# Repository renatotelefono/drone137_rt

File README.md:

# drone137

Local visual reconnaissance development for a confined space. The first runnable
product is a browser recon lab with a Python controller, a small local model
manager, and repeatable Three.js environments. No TypeScript or hosted inference is used.

**Pre-hardware build preparation:** [six-item status and evidence](docs/pre-hardware-six.md), [prototype assembly files](hardware/esp32/indoor/scout-110-bench/assembly.md) and [firmware/commissioning guide](hardware/esp32/flight/README.md). Safe builds keep motors disabled; no physical flight is qualified.
[Supported aircraft](docs/supported-aircraft.md) defines what the program can fly and the contract any aircraft must meet; the [builder brief](hardware/esp32/indoor/scout-110-bench/builder-brief.md) is the hand-off for building the Scout 110-B.

**Microquad component lab:** `/components` stores swappable parts and pinned
assemblies in SQLite, with Rapier rigid-body physics rendered by Three.js.
Run it alone with `python -m scripts.component_lab --port 8152`. The five indoor
designs and two reference variants have completed a 42-case simulation study;
unmeasured component assumptions and failed gates remain explicit. See
[data sources, engine choice, results and limitations](docs/component-physics.md).
The revised controller and explicitly revised battery hypotheses complete 40/42
flight cases (95.2%), also 400/420 across additional noise seeds. The original
assemblies remain available; hardware, camera recognition and the revised
under-$50 parts budget are not qualified by this physics benchmark.

**Ask the console:** a typed or dictated request such as "connect to the workshop scout" is mapped by the local model to one console action from a fixed list and run by the service with its usual checks; launches still go through the reviewed plan. See [mission-control.md](docs/mission-control.md).

**Docking:** a mission can end on dock A, a printed landing base with contact charging and a tag column; the aircraft returns, aligns on the tags, lands in the funnel and charges, and the dock pose becomes the map origin. Registry, dock controller API, the simulated dock and the twenty-docking gate are in [docking.md](docs/docking.md); the hardware is in `hardware/esp32/indoor/scout-110-bench/dock/`.

**Watch from the dock:** a docked aircraft keeps its camera on; motion and change are detected on every frame, the local model says what an event was from a before-and-after picture, and the console raises the alert with the evidence; whether a thing was added, taken away or moved is read from the pixels, a person is a dedicated detector's call, the model names the thing. Gated on staged synthetic events and on rendered workshop scenarios from a docked camera, the event category at 90 % on both; real clips can be recorded and played through the same gate. See [watch.md](docs/watch.md).

**Shared airspace:** several aircraft fly at once on one airspace that keeps them 1.5 m apart, gives right of way by number, holds everyone when a link goes quiet, and backs a holding aircraft out of a doorway; three aircraft gated through the benchmark room's one doorway within the 8 GB machine's budget. See [airspace.md](docs/airspace.md).

**Memory before a flight:** every plan shows what it will need against this machine, a measured preflight checks it in seconds, and the memory watch stops a mission that exceeds its budget. See [mission-control.md](docs/mission-control.md).

**Fly by hand:** a console panel for keyboard or gamepad control over the paired link, inside a reduced envelope, with release-to-level and land-on-silence; for commissioning, never for missions.

**Mission wizard:** the console opens with a Start-here panel that proposes the four mission clusters, map, audit, watch and find, from place memory and mission state, composes the brief for the one it can fly, and starts simulated exploration flights directly. See [mission-control.md](docs/mission-control.md).

**Mission control:** `/control` now connects the SQLite aircraft assembly to
Rapier flight, a service-owned Three.js camera, local Qwen plus Florence image
verification, two-view localization, return/landing and video evidence. Write a
red fire extinguisher search brief, choose an inspection area and aircraft, review
the plan and launch. Flight/recording continue when the operator dashboard closes.
One aircraft flies at a time. The rectangle selects inspection stations; transit
can leave it. Known map geometry and ideal external positioning remain assumptions.
See [mission setup, API, tests and limitations](docs/mission-runtime.md).
The Scout 110-B completed **24/24 full missions** across eight known synthetic
cases repeated three times, with zero false confirmations, decodable video and
a 4.26 GiB peak application-memory measurement on a 16 GiB host. This is separate
from the component-only physics benchmark above. See the
[full mission qualification and retained failures](docs/mission-integration-validation.md).

The earlier sequential two-aircraft, kinematic mission console remains at
`/control-legacy`. It supports inventory, doorway and view-comparison experiments.
Concurrent flight and physical control are not enabled by either dashboard.

**Unknown-place experiment:** `/places` displays environments reconstructed from
onboard RGB images and synthetic IMU data, with named places, individual visits,
maps and image-backed model observations saved in SQLite. The experimental
OpenVINS mapper starts without a room map or true-position feedback. Development
flights now pass all gates, but the latest fresh-layout suite passed only **2/3**:
one flight stopped on the link watchdog. Development-79 passes after diagnostic
I/O isolation; a new frozen suite is running. Reliable unfamiliar-environment
exploration remains open; the earlier 24/24 known-map result does not qualify it.
See [the test and current architecture](docs/blind-exploration.md) and
[preserved result summaries](docs/blind-exploration-validation.json).

**Aircraft connection:** Mission Control's **Connect a drone** panel supports
pinned HTTPS pairing, telemetry and camera preview. The ESP32 prototype firmware
now compiles, and its shared C++ controller is exercised through the host adapter
and monitor over local TLS. Recording and calibrated camera/IMU replay are
available. Physical commissioning, control tuning and autonomous-navigation
integration remain outstanding; the dashboard cannot launch a physical aircraft.
See [protocol and local setup](hardware/esp32/link-protocol.md) and the
[current handoff and remaining work](docs/agent-handoff.md).

For the first hardware prototype, use the
[Scout 110-B parts and bench build](hardware/esp32/indoor/scout-110-bench/README.md).
Its $45.09 consumed-parts allowance is not a delivered checkout quote. This
commercial-parts configuration is stored separately from the hypothetical
power-v2 aircraft used by earlier experiments. The final 24-mission qualification
uses the historical Scout 110-B assembly itself. The new printable stack has
an estimated 25.1 g structural mass; its complete mass and delivered cost are
not yet measured. Update the SQLite assembly from the built parts before using
the old simulation numbers as a hardware prediction. Physical control tuning,
component measurements and real indoor positioning remain hardware work.

**Object-location experiment:** compare the current Qwen model with Qwen plus
local Laya on a search for a red fire extinguisher. Both use camera images and
two-view bearing triangulation, with a sampled 5 GiB application-memory guard.
See [setup, protocol and limitations](docs/localization-experiment.md). This is
a separate camera-station experiment; it does not add physical flight control.

**Dense native-flight experiment:** a 120-prop workshop now runs actual PX4/Gazebo
rotor dynamics beneath the Three.js camera. Qwen and Qwen+Laya search during
continuous takeoff, transit, inspection, return and landing, with estimated-pose
triangulation, draft disturbance, telemetry and video evidence. See
[the flight-test protocol](docs/native-flight-experiment.md). The original kinematic product remains at `/control-legacy`; this native PX4 backend is an evaluation lab. The newer `/control` uses the component-based Rapier backend described above.
The [identity improvement experiment](docs/identity-improvement.md) separates
visible-part checks from triangulation and compares the 2B and 4B vision models
without loading both together. Its saved-frame diagnostic is not a real-world
qualification score.
The revised 2B full-flight batch completed 3/4 jobs with no false location
claims; 4B completed 1/4 under the same checks. A later 2B low-light repeat
passed, but the earlier miss remains evidence of inconsistent recognition.

The [real-room qualification plan](docs/real-room-qualification.md) adds a frozen
eight-mission challenge for Qwen 2B plus Laya: unfamiliar furniture arrangements,
paired present/absent targets, partial occlusion, glare/dim/blur conditions and
delayed/dropped camera frames. It also documents where offline Glob3R room
reconstruction can help, what remains unimplemented, and why a finite all-pass
test does not establish universal 100% accuracy.
Its first hard-suite Qwen + Laya run scored **5/8**, including one wrong-object
claim; all eight flights landed. Peak application guard memory was 3.48 GiB on
the 16 GiB host. The target-present success rate was 1/4, so reliable object
verification remains unresolved despite successful flight execution.

The [imported asset experiment](docs/online-assets-experiment.md) adds CC0
extinguisher, cart, shelving and crate models plus photographed workshop HDR
lighting, all bundled locally with verified hashes and aligned collision bounds.
The same Qwen 2B + Laya hard suite scored **6/8**, with two target-present
successes, one miss and one wrong-object claim. All eight flights landed;
peak application guard memory was **3.54 GiB** on the 16 GiB host. Use
`--assets polyhaven` with `scripts.evaluate_flight` to reproduce this variant.
The scene is assembled from assets, not a reconstructed real building.

The [efficiency audit](docs/efficiency.md) makes route planning 8.25× faster in
a 40-route CPU benchmark with identical paths. Fixed-input repeats reproduced
16/16 vision outputs and 22/22 Laya choices; 133 tests and a native flight smoke
test passed. This is a behavior-preserving planner optimization, not a new full
mission accuracy result or an end-to-end speedup claim.

## Start on a Mac

Requires Python 3.11–3.14 and a current browser with WebGL and MediaRecorder.
The model runtime installer targets **Apple Silicon**; Intel Macs and actual
8 GiB performance have not been validated. Local Qwen/Metal runs on the tested M4
with 16 GiB; recognition accuracy still needs improvement.

```bash
git clone https://github.com/bitfent/drone137.git
cd drone137
./scripts/bootstrap-macos.sh --minimal
./scripts/run-local.sh --mode recon --open-browser
```

Alternatively, open **Start drone137.command** in the extracted project. The
launcher bootstraps the small Python environment if missing and opens the local
console. If Finder blocks execution, run the shell commands above in Terminal.
The service binds only to `127.0.0.1:8137`; Ctrl-C stops its owned processes.

For model installation and the earlier single-aircraft smoke test, open
`http://127.0.0.1:8137/`:

1. Choose **Scripted demo · no AI**, generate a room seed, and **Start recon** to
   test rendering, navigation, recording and failure handling without model weights.
2. For local vision, install Xcode command-line tools (`xcode-select --install`),
   Git and CMake (`brew install cmake`, assuming Homebrew is already installed).
3. Click **Install runtime**, then **Download / resume model**. The manager builds
   pinned llama.cpp and retrieves Qwen3-VL-2B-Instruct Q4_K_M plus its Q8_0 vision
   projector. It pins the official model commit and verifies both SHA256 hashes.
4. **Start model**, **Test vision**, then select **Local Qwen vision** and start a
   mission. A failed vision check needs investigation before relying on observations.

The GUI exposes progress, errors, cancellation, file verification, bounded logs,
and model stop/restart. Interrupted downloads retain resumable partials. Corrupt
installed files are preserved for inspection; they are never silently used.
Keep 10 GiB free **in addition** to remaining model downloads or the 4 GiB runtime
build allowance. Actual combined resource use still needs measurement on the Mac.

## Start on Windows

Ported, not yet run on Windows: see [windows.md](docs/windows.md) for the hand-over. On a
Windows 11 x64 machine with a GPU, clone the repo and double-click `Start drone137.bat`, or in
PowerShell:

```
powershell -ExecutionPolicy Bypass -File scripts\bootstrap-windows.ps1 --minimal
scripts\run-local.ps1 --mode recon --open-browser
```

The console's "Install runtime" unpacks a pinned llama.cpp release (Vulkan by default, CUDA or
CPU with `DRONE137_RUNTIME_BACKEND`); the person detector comes from
`python -m scripts.fetch_person_model`.

## What the virtual product does

- Generates repeatable random rooms, warehouse aisles and connected rooms.
- Runs inspection-point patrols with baseline and obstructed-passage variants;
  returns with a partial report when an inspection point cannot be reached.
- Simulates ideal pose and planar range sensing; builds an observed occupancy map.
- Plans clearance-aware routes through observed free cells, explores new areas,
  and returns home after up to 12 observations. Mission deadline: 180 seconds.
- Provides overhead and onboard cameras. The local model sees selected fresh
  320 × 240 JPEGs and can continue, request one additional left/right view, hold,
  or finish an exploration. Patrols restrict it to continue, extra views or hold;
  one blank view cannot finish the whole patrol. The model cannot issue arbitrary
  coordinates or motor commands.
- Runs range supervision independently of inference; sensor loss, browser/camera
  loss, inference errors and operator intervention stop motion.
- Records browser video (WebM or MP4), selected images, pose/event timestamps,
  scene seed and observations. Saved missions open an HTML report with video
  seek links, images, observed map, route and unreached points. Matching local-model
  patrols compare independently classified images at aligned viewpoints and flag
  a new obstruction when open space becomes a solid surface. Evidence shares a 1 GiB cap.

The mission-control dashboard is a **fixed-altitude kinematic sandbox**. The
separate native-flight evaluation lab above uses PX4/Gazebo dynamics; neither
path has been qualified against a physical aircraft.
Map-observed percentage is geometric sensor coverage, not camera visibility or
semantic recognition accuracy. Sensors/pose are ideal; there is no SLAM, sensor
noise, dynamic-obstacle prediction, full 3D planning or physical drone connection.
Observation seek links use approximate browser video time; exact exposure/pose
alignment remains unverified.
Pause ends autonomous progress; end the mission before starting another. Keep the
browser tab active: camera/browser loss stops the virtual mission after 2 seconds.

## Validation and current limits

**Simulation versus real-drone comparison:** [test data and comparison tables](docs/test-comparison.md)
preserve Scout 110-B component/mission results, blind-mapping failures, the
historical vision-model comparison and separate software-test counts. A
[frozen JSON baseline](docs/test-data/pre-hardware-2026-10-23.json) retains exact
values and source hashes, and a [physical-run template](docs/test-data/hardware-run-template.json)
is ready for measured hardware results. No physical flight results exist yet;
unmeasured values stay empty rather than being presented as passes.

Real-world reliability is now tracked separately for **workshops, warehouses,
building perimeters, flat fields and hillsides**. All five remain unqualified.
The frozen real-camera smoke test found 11 of 12 labelled object names across six
public indoor images, with one missed object group. This is diagnostic evidence,
not a general accuracy or flight claim. The [reliability protocol](docs/reliability-protocol.md)
defines data collection, site separation, proposed thresholds and commands to
evaluate local camera clips without flying a drone. Full-caption precision and
site-specific data remain missing.

Current Mac and historical Linux evidence is in [docs/validation.md](docs/validation.md).
The M4 build ran actual Qwen/Metal patrols, recorded playable video and generated
reports. The original closed-gate and changed-passage misses are retained as
regressions. Separating image evidence from action selection, with settings for each camera
profile, passes all 32 center-classification cases (24 rendered views plus eight regressions), with
zero blocked views classified as open. Successful recording/navigation alone does
not prove perception accuracy; the patrol browser test also checks recognition.
104 accelerated geometry scenarios returned with zero clearance violations. A
separate real-Qwen PX4/Gazebo gate route correctly classified both gates and
returned to land; indoor patrol is not yet connected to that dynamics backend.
The GUI reports failures explicitly and never switches to scripted decisions itself.

For richer visual inspections, choose **Detailed workshop · 720p → Baseline →
Patrol inspection points**. The scene contains stocked shelving, labeled cartons,
a workbench with monitor/keyboard/toolbox/vise/cable, drums on a pallet, a hand
truck, tool drawers, a plant and a fire extinguisher. Geometry and canvas labels
are generated locally; there are no runtime asset downloads. The report adds a
whole-image object description and visible uncertainty beside each camera image.

The workshop records **1280 × 720 at a requested 15 fps**, with **960 × 540** model
snapshots. Its 41° vertical field of view approximates the standard Camera Module 3
candidate in the project brief ([manufacturer specifications](https://www.raspberrypi.com/documentation/accessories/camera.html)).
This is an ideal rendered camera, not a calibrated physical-camera or photorealism
benchmark. Use **Enlarge camera** to inspect the detail. Older simple scenes retain
their 320 × 240 profile.

Choose **Camera realism bay · 720p** for bottles, a wheeled chair and a safety cone
alongside the stocked workshop and cluttered bench. Its local scanned concrete
maps add surface detail. **Camera conditions** selects nominal, low light, glare,
or blur/shift stress. The camera points down 10°; exposure, noise, blur, lens warp
and vignetting are synthetic settings, not hardware calibration. The displayed
camera, recorded video and model snapshots share that processed image. Conditions
are saved in each report and must match when selecting a comparison baseline.
Geometry/range sensing and fixed-height motion still use the ideal sandbox.

To try the product: choose **Warehouse aisle → Baseline → Patrol inspection points**,
start a patrol, open its report, then load **Passage obstructed** and repeat. Use
Local Qwen for observations, or Scripted demo to test the pipeline without inference.

The [Mac handoff](docs/handoff.md) contains transfer, startup and acceptance steps.
[Recon objective](docs/recon-objective.md) separates implemented workflow from the
remaining localization, camera-coverage and flight-dynamics work.

## Development

```bash
# Linux/cloud, or a development machine with Python 3.11–3.14:
./scripts/bootstrap-cloud.sh --minimal
./scripts/test-portable.sh
./scripts/run-local.sh --mode recon
# A second terminal can stop this app:
./scripts/stop-local.sh
```

Three.js 0.180.0 is vendored with its MIT licence and verified npm integrity
metadata, so the GUI does not require Node, npm or a CDN at runtime. Python
packages are installed from hash-locked requirements. Source export:

```bash
./scripts/export-handoff.sh
```

`dist/drone137-source.tar.gz` and its checksum sidecar exclude model weights,
virtual environments, native builds, caches and bulk run evidence. Configurable
paths: `DRONE137_DATA_DIR` (default `.local/data`) and `DRONE137_BUILD_DIR`
(default `.local/build`). Completed runs remain under `.local/data/runs/<episode>`;
no automatic evidence deletion occurs.

Optional browser integration test, using an installed Chromium:

```bash
npm install --prefix .local/browser-test playwright@1.58.2
# With the recon app running; set CHROMIUM_PATH for your browser:
CHROMIUM_PATH="/Applications/Google Chrome.app/Contents/MacOS/Google Chrome" node scripts/check-browser.cjs
# Two rendered warehouse patrols; real Qwen must already be running:
DRONE137_TEST_POLICY=qwen node scripts/check-patrol.cjs
# Fresh rendered perception cases, scored with the same production model pipeline:
node scripts/render-vision-cases.cjs
.venv/bin/python -m scripts.evaluate_perception
# Detailed camera/object recognition and complete workshop patrols:
node scripts/render-detail-cases.cjs
.venv/bin/python -m scripts.evaluate_detail
DRONE137_TEST_POLICY=qwen DRONE137_TEST_SCENARIO=workshop node scripts/check-patrol.cjs
# Accelerated navigation-only suite, no browser/model/dynamics:
.venv/bin/python -m scripts.evaluate_recon --episodes 100
# Production camera stress set (local model ready, no active mission):
DRONE137_REALISM_CASES=.local/validation/my-realism-cases node scripts/render-realism-cases.cjs
.venv/bin/python -m scripts.evaluate_reliability freeze --manifest .local/validation/my-realism-cases/manifest.json --lock .local/validation/my-realism-cases/frozen.json
.venv/bin/python -m scripts.evaluate_reliability run --manifest .local/validation/my-realism-cases/manifest.json --lock .local/validation/my-realism-cases/frozen.json --output .local/validation/my-realism-results
DRONE137_TEST_POLICY=qwen DRONE137_TEST_SCENARIO=realism node scripts/check-patrol.cjs

# Frozen real-image/recorded-video evaluation: see docs/reliability-protocol.md
.venv/bin/python -m scripts.evaluate_reliability --help
```

The scripted browser check exercises a full mission, decodes its video, runs a
sensor failure mission. Set `DRONE137_EXPECT_MODEL_NETWORK_BLOCK=1` only on this
restricted cloud network to also exercise its expected HTTP 403 download error. It is an optional developer check, not a product dependency.

Legacy gate fixture:

```bash
./scripts/run-local.sh --mode fixture --profile cloud-dev --policy scripted
./scripts/evaluate.sh --suite smoke --mode fixture --episodes 2
```

Native Gazebo/PX4 gate integration remains experimental and requires separate
large installations. See `docs/handoff.md`; it does not yet implement indoor recon.

The [hardware realism workbench](docs/hardware-realism.md) adds a SQLite aircraft
library, frozen quadcopter profiles, parameterized optics, GPS-disabled native
sensor emulation, observed-map routing and offline camera/room/motor calibration
tools. Open `/airframes` from mission control. Profiles are provisional until
measurements are supplied; native comparisons run sequentially.

The optional live vision comparison flies Qwen alone, Qwen + Florence-2-base-ft,
and Qwen + SmolVLM2-500M through the same four glare/occlusion missions, including
target-absent controls. Each companion receives live camera crops; Qwen supervises
search in all three arms. The aircraft must first pass measured rotor-joint,
lift-off, hover and landing checks. This is a synthetic development benchmark,
not physical-world qualification. The application guard is 5 GiB, leaving intended
headroom on an 8 GB host; actual 8 GB hardware still requires validation.

```bash
python3.12 -m venv .local/vision-env
.local/vision-env/bin/python -m pip install -r requirements-vision-reviewers.txt
.local/vision-env/bin/python scripts/download_vision_reviewers.py
# Requires the existing native simulator, camera runtime and idle local Qwen app.
.local/laya-env/bin/python -m scripts.evaluate_flight \
  --output .local/validation/my-aircraft-check --suite realism --assets polyhaven \
  --airframes reference-quad@1 --navigation observed --smoke \
  --cases realism-east-motion-present
.local/laya-env/bin/python -m scripts.compare_vision_flights \
  --output .local/validation/my-vision-flight-comparison \
  --preflight .local/validation/my-aircraft-check/results.json
```

Use new output directories for each attempt. Reports retain failed missions and
separate physical flight checks, targets found, false location claims, latency,
memory and full acceptance. Checkpoint revisions and file hashes are recorded.

Measured live results and their limits are in
[the flight comparison](docs/vision-flight-comparison.md). For a separate bounded
closer-view experiment, add `--inspection-policy active-v2` to `evaluate_flight`.
This changes evidence acquisition while retaining the original identity gates;
keep it separate from comparisons of models under the default inspection policy.

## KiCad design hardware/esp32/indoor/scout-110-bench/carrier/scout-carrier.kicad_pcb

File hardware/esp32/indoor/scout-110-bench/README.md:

# Build choice: D137 Scout 110-B

**Swiss procurement (24 October):** [procurement-ch.md](procurement-ch.md) lists Swiss sources, prices, stock and the two substitutions found.

**24 October build update:** [Prototype A assembly package](assembly.md) now includes the schematic, routed carrier, Gerbers and five printable parts. [Flight firmware and commissioning tools](../../flight/README.md) compile and have software tests. Physical fit, power, timing and flight tuning remain unmeasured. The old mass/profile results below are historical and do not qualify the revised mechanical stack.

Build one **Scout 110-B bench prototype** first: a guarded 110 mm quadcopter,
four brushed 8520 motors, a forward-facing XIAO ESP32-S3 Sense camera, and a
single commercial 1S battery. The local computer runs Drone137, Qwen and Florence.
The prototype firmware implements onboard stabilization and command-loss handling;
its physical tuning and timing still need measurement.
No Jetson, onboard language model, Internet connection or mesh network is required.

This is a specific parts choice for camera, electrical and mechanical development.
It is **not a flight-ready kit**: the carrier and firmware are implemented, but
physical fit, electrical performance, control tuning and real indoor positioning
remain unvalidated. The default flight build keeps motor outputs disabled.
Start with camera/IMU recording and frame fit using the current assembly guide.

## Parts to obtain

Core vendor listings rechecked 23 October 2026. USD except where explicitly stated. The
machine-readable [bill of materials](bom.json) records quantities and price bases.

| Part | Quantity | Cost per aircraft | Purchase reference / basis |
|---|---:|---:|---|
| XIAO ESP32-S3 Sense, supplied camera and antenna | 1 | $13.90 | [Seeed SKU 113991115](https://www.seeedstudio.com/XIAO-ESP32S3-Sense-p-5639.html) |
| GY-521 MPU-6050, 3–5 V module input | 1 | $4.95 | [Qkits SKU MPU-6050](https://store.qkits.com/electronics/3-axis-gyroscope-accelerometer-gy-521.html), USD listing |
| 8520 motors, 1 mm shafts, 2 CW + 2 CCW | 4 | $9.00 allowance | [Unmanned Tech 41C-069-230](https://www.unmannedtechshop.co.uk/products/8520-coreless-brushed-motor-pack-2-x-cw-2-x-ccw), actual listing £6.49 per four-pack |
| HQProp 65 mm ultralight, 1 mm shaft, 2 CW + 2 CCW | 4 | $2.39 | [SpeedyFPV TR21](https://speedyfpv.com/products/hqprop-65mm-ultralight-propeller-set-2x-cw-2x-ccw-gray) |
| BETAFPV 450 mAh 1S BT2.0 pack, SKU 01030002 | 1 | $3.75 allocated | [BETAFPV four-pack $14.99](https://betafpv.com/collections/batt-1s/products/bt2-0-450mah-1s-30c-battery-4pcs) |
| Scout 110 printed structure with guards | Set | $4.00 historical allowance | Use the [Prototype A five-part package](assembly.md); obtain its actual print price |
| AO3400A MOSFETs | 4 | $1.00 allowance | SOT-23, low-side motor switches |
| SS34 Schottky diodes, SMA package | 4 | $0.60 allowance | One flyback diode per motor; the carrier footprint is SMA (DO-214AC), so use an SMA-packaged SS34 (for example MDD) or MBRA340T3G |
| 100 ohm gate resistors + 10 kohm pulldowns | 4 + 4 | $0.20 allowance | One of each per MOSFET |
| Motor suppression and supply capacitors | Set | $0.70 allowance | 4 × 100 nF; 470 uF ≥6.3 V; 47 uF; 100 nF |
| Battery measurement divider/filter | Set | $0.10 allowance | 2 × 100 kohm and 100 nF |
| Carrier, IMU mount and connections | Set | $3.00 allowance | Material only; PCB layout/tooling not included |
| BT2.0 aircraft pigtail, wire, camera mount, strap and fasteners | Set | $1.50 allowance | Short motor-current paths; strain relief |
| **Total consumed parts allowance** | | **$45.09** | **A budget, not a complete retail checkout quote** |

The battery seller requires a four-pack. Buying that pack adds $11.24 of spare
battery inventory, making the listed first-build purchase allowance **$56.33
before shipping, taxes and other order minimums**. A delivered single prototype
under $50 has not been established. The $45.09 figure is per aircraft consumed
parts and includes some unquoted allowances. The motor USD allowance is not a
currency conversion guarantee. Charger, tools, ground computer, Wi-Fi access
point, positioning equipment, labour, PCB engineering and spares are excluded.

The original SpeedyFPV $4.49 motor/propeller kit is sold out in its live product
inventory. Do not base this build on that sale price. The replacement motor pack
and HQProp set were available when checked; their combined loaded thrust/current
has not been published or measured here.

## First-prototype order — 23 October 2026

Order **one prototype**, with spare batteries from the required multipack. Buy the
unsoldered **Sense** camera version of the XIAO; the plain ESP32-S3 board does not
include the camera. The camera streams over local Wi-Fi to the ground computer.

| Order now | Purchase quantity | Listed order price |
| --- | ---: | ---: |
| [Seeed XIAO ESP32-S3 Sense](https://www.seeedstudio.com/XIAO-ESP32S3-Sense-p-5639.html) | 1 | $13.90 |
| [Qkits GY-521 MPU-6050](https://store.qkits.com/electronics/3-axis-gyroscope-accelerometer-gy-521.html) | 1 | $4.95 |
| [Unmanned Tech 8520 motor pack, 2 CW + 2 CCW, 1 mm shafts](https://www.unmannedtechshop.co.uk/products/8520-coreless-brushed-motor-pack-2-x-cw-2-x-ccw) | 1 four-pack | GBP 6.49 |
| [HQProp 65 mm, 1 mm hub, 2 CW + 2 CCW](https://speedyfpv.com/products/hqprop-65mm-ultralight-propeller-set-2x-cw-2x-ccw-gray) | 1 four-pack | $2.39 |
| [BETAFPV 450 mAh 1S BT2.0 batteries](https://betafpv.com/collections/batt-1s/products/bt2-0-450mah-1s-30c-battery-4pcs) | 1 four-pack; fit one battery | $14.99 |
| [BETAFPV BT2.0 Whoop Cable Pigtail](https://betafpv.com/collections/accessories/products/bt2-0-1s-whoop-cable-pigtail) — select **BT2.0 Cable Pigtail**, SKU 00313631 | 1 six-pack; fit one pigtail | $5.99 |

This core order totals **$42.22 plus GBP 6.49**, before frame, carrier, small
electronics, shipping and taxes. This is not the complete aircraft checkout.
The motor, propeller and charger stock/price were also checked against their
retailers' public product-variant data; all were available at the time of checking.
An extra propeller set is useful but is not included in the subtotal.

The remaining electrical parts are listed below so they can be sourced together.
The [Prototype A carrier BOM](assembly.md#populate-the-carrier) now specifies packages and wiring. Physical package fit, supply ripple, current handling and assembled mass still require measurements. Small-component prices
and minimum quantities must be reconfirmed in the cart.

| Component reference | Quantity used on one aircraft | Ordering note |
| --- | ---: | --- |
| [AOS AO3400A, SOT-23, LCSC C20917](https://www.lcsc.com/product-detail/MOSFETs_Alpha-Omega-Semicon_C20917.html) | 4 | Listed minimum 5, about $0.43 per five |
| [MDD SS34, SMA, LCSC C8678](https://www.lcsc.com/product-detail/C8678.html) | 4 | Listed minimum 20, about $0.70 per twenty |
| [100 ohm, 0805, 1%, C17408](https://www.lcsc.com/product-detail/C17408.html) | 4 | MOSFET gate resistors |
| [10 kohm, 0805, 1%, C17414](https://www.lcsc.com/product-detail/C17414.html) | 4 | MOSFET gate pulldowns |
| [100 kohm, 0805, 1%, C149504](https://www.lcsc.com/product-detail/C149504.html) | 2 | Battery measurement divider |
| [100 nF, 50 V X7R, 0805, C1711](https://www.lcsc.com/product-detail/C1711.html) | 6 | Four motor suppression, one electronics decoupling, one ADC filter |
| [470 uF, 10 V, SAMYOUNG KMG, C349987](https://www.lcsc.com/product-detail/Aluminum-Electrolytic-Capacitors-Leaded_SamYoung-Electronics_C349987.html) | 1 | Provisional motor-supply bulk capacitor; validate ripple/ESR under motor load |
| [47 uF, 10 V, SAMYOUNG CLZ, C41428003](https://www.lcsc.com/product-detail/C41428003.html) | 1 | Provisional electronics supply capacitor |
| [26 AWG silicone wire](https://www.adafruit.com/category/product/1970) | Short signal/individual motor leads as needed | Reuse supplied motor leads; keep the main battery lead at the pigtail's 22 AWG |

Print one of each of the five [Prototype A parts](assembly.md#fabrication-files)
for **dry fitting**. This package replaces the earlier single-frame proposal.
The frame and camera/battery mounting are not mechanically qualified. Check
the purchased component dimensions before ordering a batch; physical fit and
current handling remain unverified. Reprice the revised stack and carrier;
the historical $45.09 allowance is not a quote for the new fabrication package.

Shared bench equipment, separate from aircraft cost:

- [VIFLY WhoopStor 3](https://viflydrone.com/collections/lipro-battery-charger/products/vifly-whoopstor-6-ports-1s-battery-storage-charger-discharger),
  $32.99: BT2.0 charging with selectable 4.20 V. Start at **4.20 V / 0.3 A** for
  this 450 mAh pack. It needs a suitable power source; use a compatible USB-C PD
  supply meeting the manufacturer's 40 W input specification, not a plain 5 V
  USB port. Reuse a suitable supply if already owned. The manufacturer charger
  plus 65 W US supply bundle was unavailable when checked.
- USB-C **data** cable for flashing, soldering equipment, a multimeter, and a
  scale for assembled mass/thrust measurements. Reuse existing tools. Initial
  camera/IMU checks and motor-output checks are performed without propellers.

The earlier $45.09 consumed-parts estimate is retained above for traceability.
It is not a promise of a delivered build below $50; charger, spare inventory and
multiple sellers' shipping alone make that an inappropriate first-order budget.

## Work required before the first flight

1. Fabricate and inspect the Prototype A carrier, dry-fit the printed parts, and document the as-built wiring, motor order and sensor orientation.
2. Flash the motors-disabled prototype flight firmware and verify the implemented IMU, battery and camera paths on the board. Then follow the propeller-free and restrained commissioning stages; verify control timing while camera streaming is active.
3. Connect physical timestamped camera/IMU telemetry to Drone137; validate stale
   data rejection, exclusive control, operator stop and link-loss behaviour on
   the actual board. Host tests against the protocol emulator do not do this.
4. Measure mass, propulsion/current, battery sag and vibration; update the SQLite
   component revisions and repeat the relevant simulations. Complete restrained
   motor/control checks before a brief guarded hover in a protected test space.
5. Demonstrate real indoor position/height feedback and recovery before enabling
   room navigation or mapping. The MPU-6050 is not an indoor position sensor.
   Additional navigation hardware is not yet specified or included in this order.

Current readiness: **parts procurement and camera bench work can begin; physical
flight remains disabled and unqualified**. There has been no hardware flight.

Use the [simulation/real-drone comparison section](../../../../docs/test-comparison.md)
to retain the existing baseline and record the physical measurements. It includes
exact historical results, configuration/source hashes and a blank physical-run
template. Do not overwrite earlier results when measured components are added.

## Battery and mass

Use **one purchased 1S pack**, not a home-built parallel pack. Limit charging to
**4.20 V** for the initial aircraft electronics/motor design. Although this cell
is sold for 4.35 V charging, the current component model limits propulsion to
4.20 V; a 4.35 V fully charged pack is outside this build configuration.
Use a suitable external BT2.0 1S charger set to 4.20 V. Disconnect the flight
battery during initial USB camera setup.

The manufacturer lists 12.7 g for the pack. The registry adds a provisional 1 g
pigtail, estimates usable capacity at 400 mAh under the lower charge limit, and
assumes 0.10 ohm pack resistance. **Capacity and resistance are hypotheses**, not
manufacturer specifications. The historical assembled mass hypothesis is
**63.26 g**, before the revised printable stack. That stack alone has a geometric
25.1 g solid-PETG estimate. Weigh the real prints, wires, boards and pack and
create a new SQLite assembly revision before predicting this prototype's flight.

The tested `scout-110-power-v2` simulation uses a different, hypothetical 1S2P
480 mAh pack. Its mission result must not be transferred to this purchase build.
`scout-110-bench-b@1` is registered separately in SQLite with frozen component
references and explicit evidence labels. Both configurations remain disabled for
physical operation.

The final **qualification-04** batch tested this Scout 110-B assembly directly:
**24/24 complete simulated missions passed**, with zero false confirmations and
zero missed targets. Peak application memory was 4.26 GiB on a 16 GiB host;
actual 8 GB hardware remains untested. Largest location error was 0.662 m against
the unchanged 0.75 m tolerance; the longest mission took 287 seconds against a
300-second deadline. See the [full qualification](../../../../docs/mission-integration-validation.md).
These are three repeats of eight known synthetic cases with an ideal external
position reference and full modeled batteries, not real-world flight validation.

The initial component-only run completed six 20-second scenarios: **5/6 flight
checks passed**. Nominal, gust, link loss, weak motor and pessimistic assumptions
completed; low battery failed. Only **4/6** met the separate 2:1 thrust-reserve
engineering gate. See [the complete results](simulation-checks.json). These use
estimated propulsion and battery parameters, test no image recognition, and do
not establish readiness for physical flight.

## Assemble and bring up in this order

1. **Camera and IMU first, motors disconnected.** Order the Sense version with
   its camera and antenna. Provision and flash the default motors-disabled
   [flight firmware](../../flight/README.md), then connect/record from Drone137.
   Record the actual camera sensor/revision, verify focus and orientation, then
   measure frame latency. The older `camera_bench.ino` remains a separate
   camera-only diagnostic; it does not implement the flight protocol.
2. **Print and dry-fit the frame.** Motor diagonal 110 mm, nominal 8.6 mm bores,
   65 mm propellers with 1 mm hubs. Adjust bores to the actual print and motor.
   Check propeller/guard clearance, shaft engagement and guard stiffness. The
   CAD is an unprinted dimensional prototype. Centre the battery beneath the
   plate and keep the camera and antenna clear of props and motor wiring.
3. **Build the electrical carrier with the propellers removed.** Follow the
   [Prototype A wiring schedule](assembly.md#wiring-and-motor-orientation).
   The ESP32
   GPIO drives a MOSFET gate, never a motor directly. Verify the actual IMU board
   input regulator and 3.3 V I2C levels; confirm its chip identity and orientation.
4. **Measure the exact propulsion and pack.** Record per-motor thrust/current/RPM
   versus duty and loaded voltage, pack sag/capacity, assembled mass and geometry.
   Save new component revisions in `/components`, preserving the original data.
   Repeat the simulation with those revisions. A different motor winding or prop
   pitch is a new propulsion measurement, even when its dimensions are identical.
5. **Flight-control bench testing precedes flight.** Measure and tune the
   implemented IMU estimator, onboard rate loop/mixer, bounded commands,
   telemetry, battery monitoring and command-loss behavior under simultaneous
   Wi-Fi camera load. Real position feedback must replace the simulator's ideal
   reference before room navigation. Begin subsequent flight tests in a protected
   test space after these checks; simulation success alone is not that validation.

## What the simulation proves and what it assumes

The software test flies a component model through a detailed rendered room and
uses local models to inspect its camera images. Known room geometry and an ideal
external position reference remain inputs. It does not prove that an MPU-6050
alone supplies room coordinates, that the selected Wi-Fi camera maintains the
simulated quality, or that a cheap quad can fly autonomously without additional
positioning work. The benchmark images are 960 × 540; current camera bench code
uses 640 × 480. Re-run recognition at the measured real camera settings.

The hardware path is camera → local Wi-Fi → Drone137 on the ground PC → bounded
flight commands → onboard flight controller. The rapid stabilization loop belongs
on the drone, and the language models inspect images and propose mission actions
on the computer. The prototype firmware/host path now has software tests and
board builds; physical mission navigation remains disabled pending measurements.

## Dock

`dock/` holds dock A: a printed funnel base with contact charging and a tag stand, so
the Scout lands, recharges and takes off again without a battery swap. Geometry, wiring,
Swiss parts and the aircraft-side changes are in `dock/README.md`,
`procurement-ch.md` and `assembly.md`; the flight procedure is `docs/docking.md`.

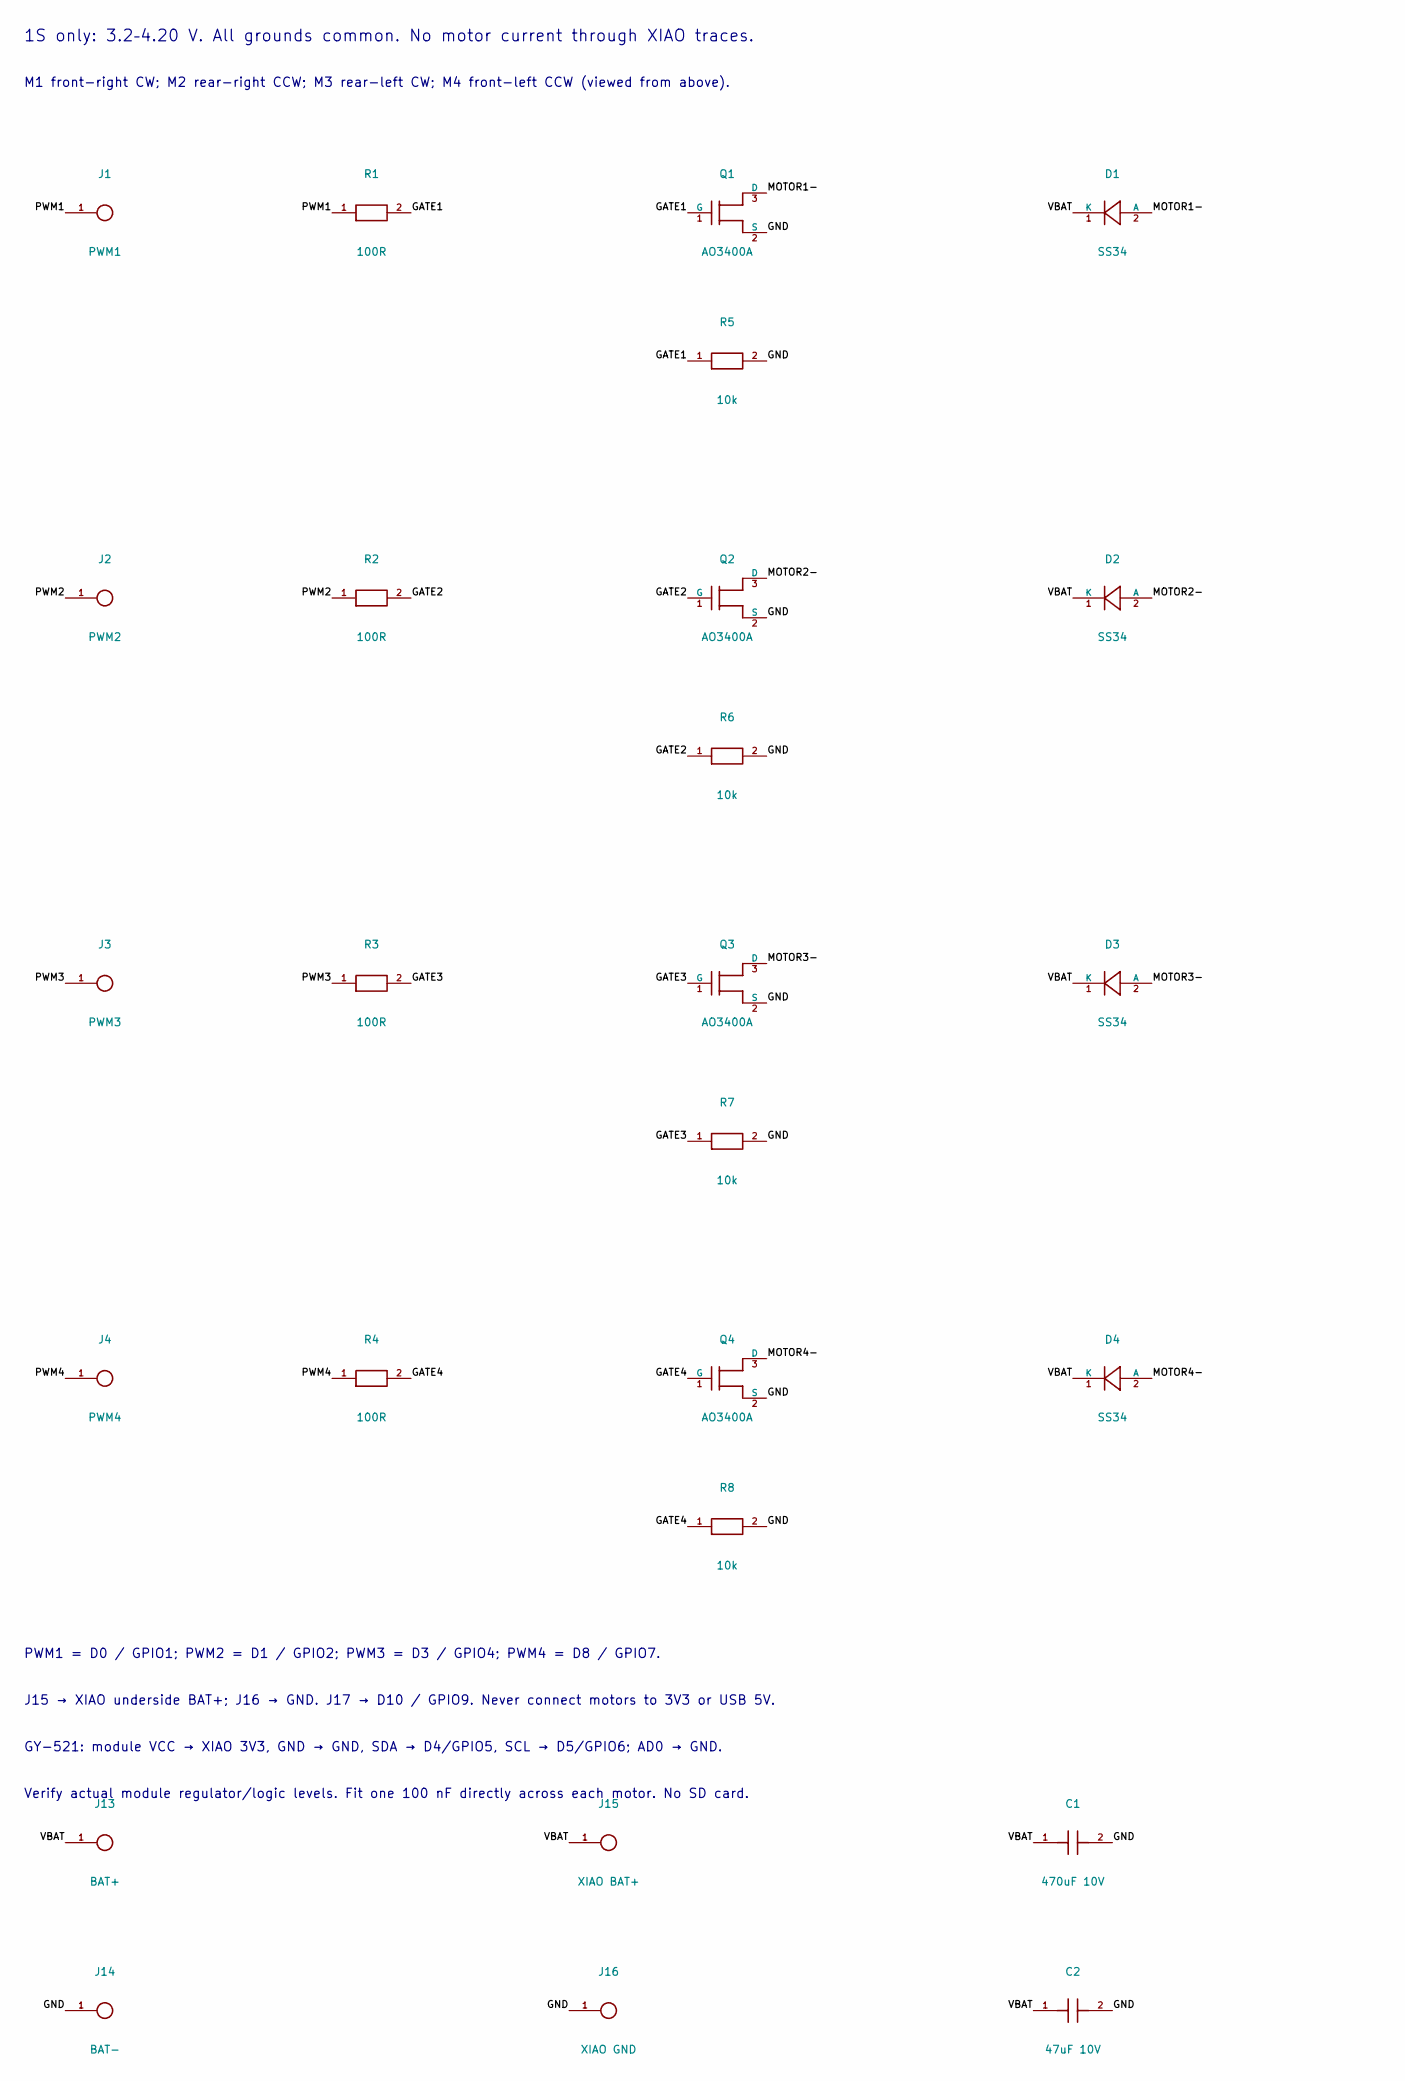
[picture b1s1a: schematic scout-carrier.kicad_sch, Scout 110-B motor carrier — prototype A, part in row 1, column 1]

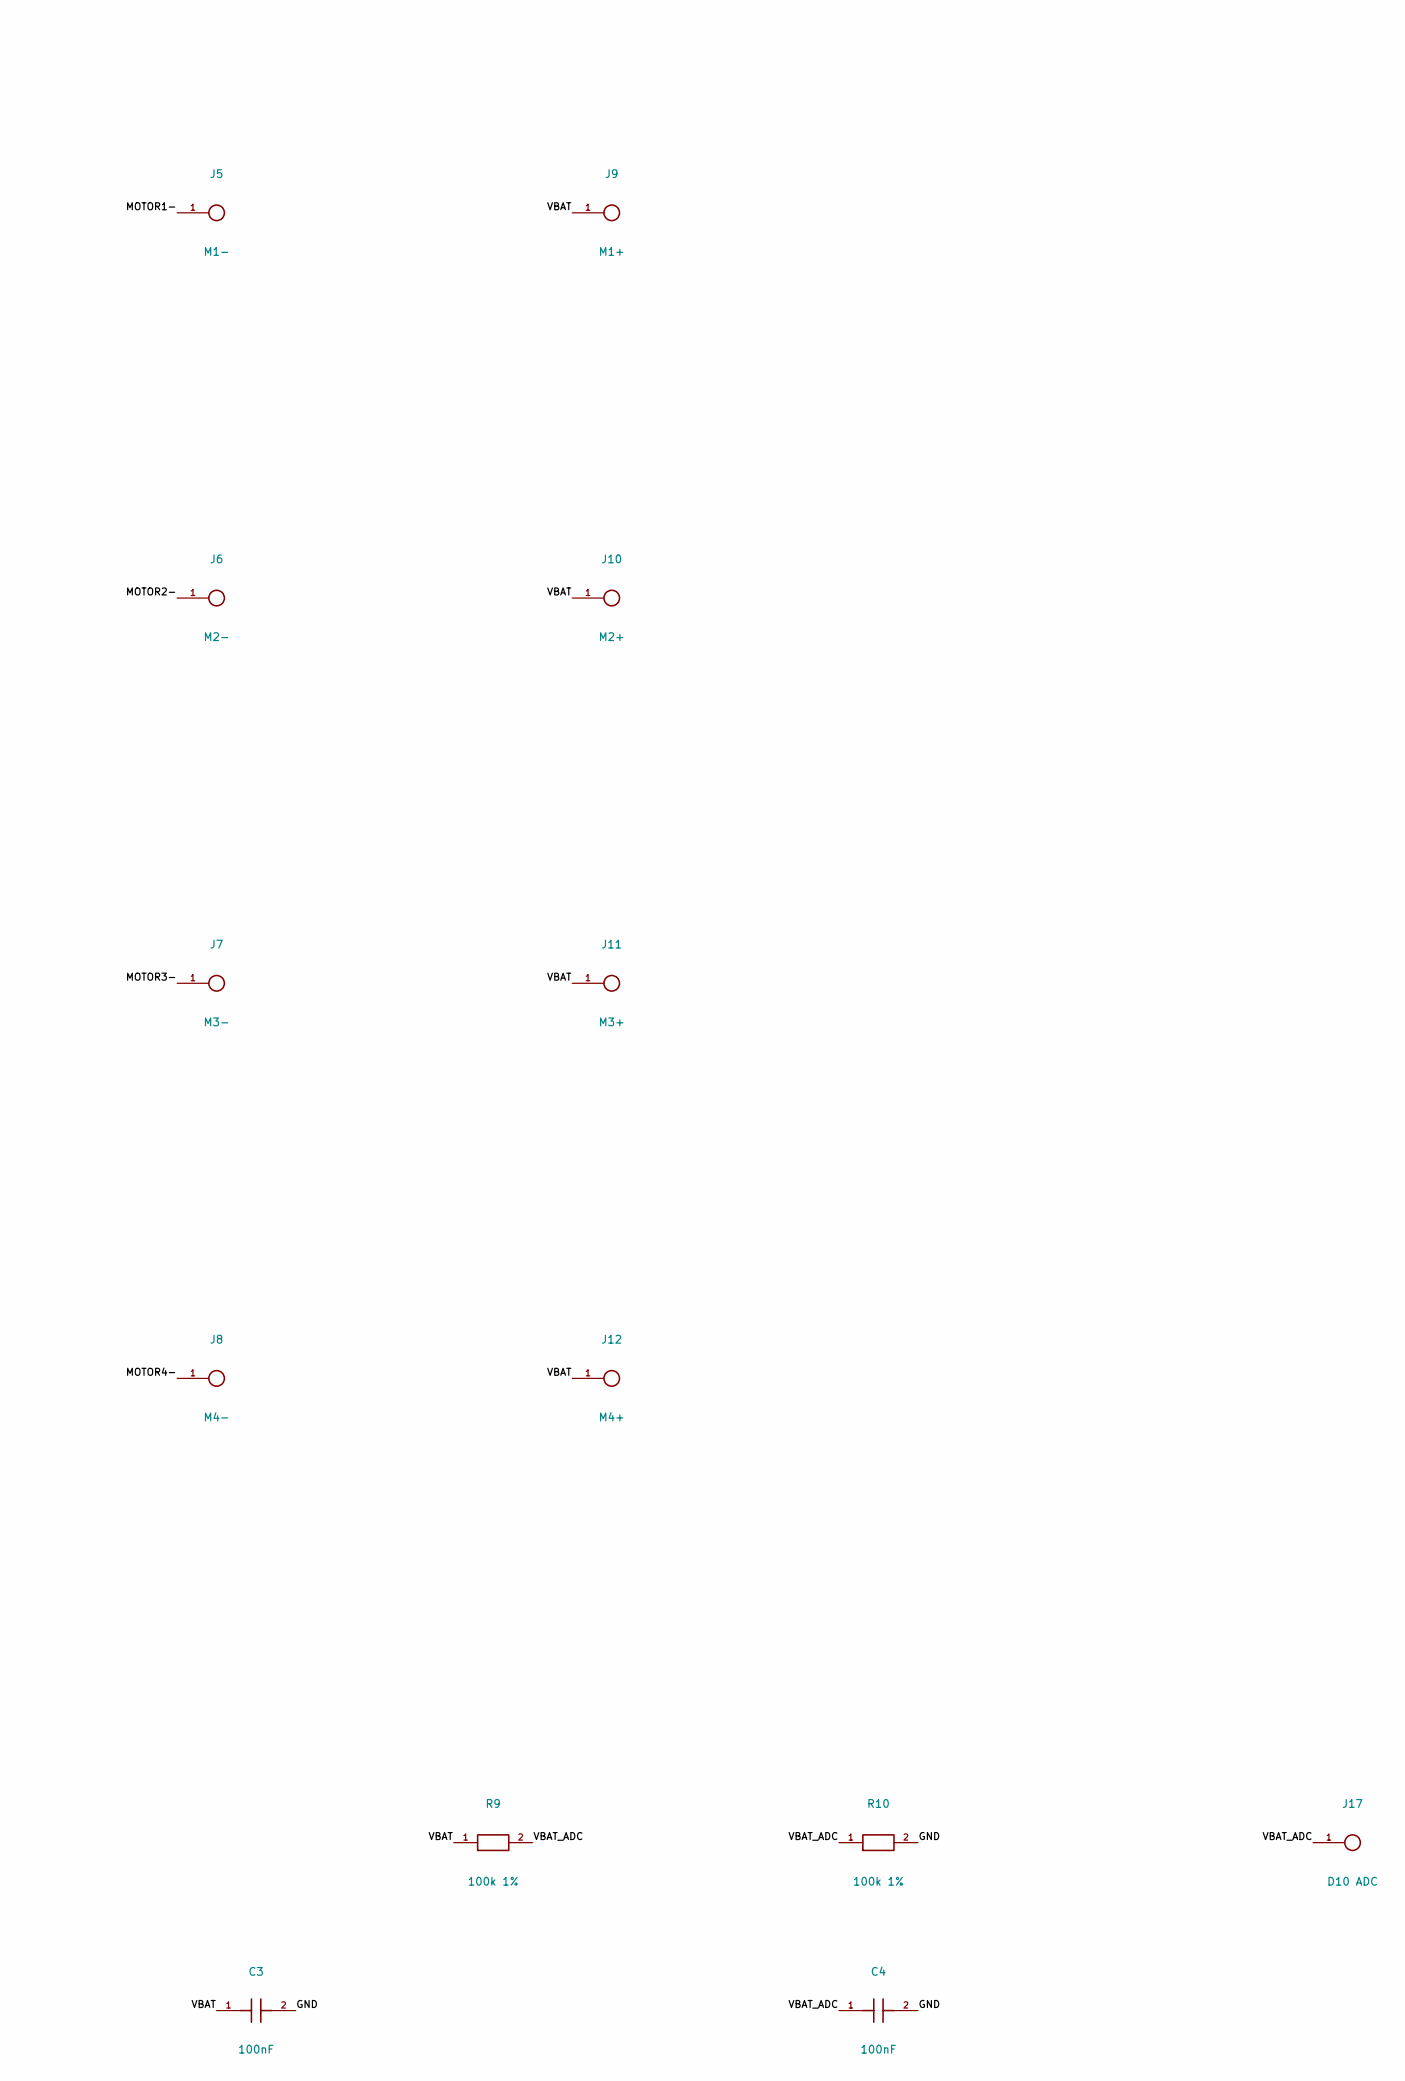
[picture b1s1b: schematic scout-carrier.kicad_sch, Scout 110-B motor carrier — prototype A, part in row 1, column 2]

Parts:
C1: 470uF 10V; CP_Radial_D6.3mm_P2.50mm
C2: 47uF 10V; CP_Radial_D5.0mm_P2.00mm
C3, C4: 100nF; C_0805_2012Metric
D1, D2, D3, D4: SS34; D_SMA
J1: PWM1; WirePad_1.6_0.8
J2: PWM2; WirePad_1.6_0.8
J3: PWM3; WirePad_1.6_0.8
J4: PWM4; WirePad_1.6_0.8
J5: M1-; WirePad_2.1_1.0
J6: M2-; WirePad_2.1_1.0
J7: M3-; WirePad_2.1_1.0
J8: M4-; WirePad_2.1_1.0
J9: M1+; WirePad_2.1_1.0
J10: M2+; WirePad_2.1_1.0
J11: M3+; WirePad_2.1_1.0
J12: M4+; WirePad_2.1_1.0
J13: BAT+; WirePad_2.8_1.2
J14: BAT-; WirePad_2.8_1.2
J15: XIAO BAT+; WirePad_2.1_1.0
J16: XIAO GND; WirePad_2.1_1.0
J17: D10 ADC; WirePad_1.6_0.8
Q1, Q2, Q3, Q4: AO3400A; SOT-23
R1, R2, R3, R4: 100R; R_0805_2012Metric
R5, R6, R7, R8: 10k; R_0805_2012Metric
R9, R10: 100k 1%; R_0805_2012Metric

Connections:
GATE1: Q1.1 (G), R1.2, R5.1
GATE2: Q2.1 (G), R2.2, R6.1
GATE3: Q3.1 (G), R3.2, R7.1
GATE4: Q4.1 (G), R4.2, R8.1
GND: C1.2, C2.2, C3.2, C4.2, J14.1, J16.1, Q1.2 (S), Q2.2 (S), Q3.2 (S), Q4.2 (S), R5.2, R6.2, R7.2, R8.2, R10.2
MOTOR1-: D1.2 (A), J5.1, Q1.3 (D)
MOTOR2-: D2.2 (A), J6.1, Q2.3 (D)
MOTOR3-: D3.2 (A), J7.1, Q3.3 (D)
MOTOR4-: D4.2 (A), J8.1, Q4.3 (D)
PWM1: J1.1, R1.1
PWM2: J2.1, R2.1
PWM3: J3.1, R3.1
PWM4: J4.1, R4.1
VBAT: C1.1, C2.1, C3.1, D1.1 (K), D2.1 (K), D3.1 (K), D4.1 (K), J9.1, J10.1, J11.1, J12.1, J13.1, J15.1, R9.1
VBAT_ADC: C4.1, J17.1, R9.2, R10.1

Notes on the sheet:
1S only: 3.2–4.20 V. All grounds common. No motor current through XIAO traces.
M1 front-right CW; M2 rear-right CCW; M3 rear-left CW; M4 front-left CCW (viewed from above).
PWM1 = D0 / GPIO1; PWM2 = D1 / GPIO2; PWM3 = D3 / GPIO4; PWM4 = D8 / GPIO7.
J15 → XIAO underside BAT+; J16 → GND. J17 → D10 / GPIO9. Never connect motors to 3V3 or USB 5V.
GY-521: module VCC → XIAO 3V3, GND → GND, SDA → D4/GPIO5, SCL → D5/GPIO6; AD0 → GND.
Verify actual module regulator/logic levels. Fit one 100 nF directly across each motor. No SD card.

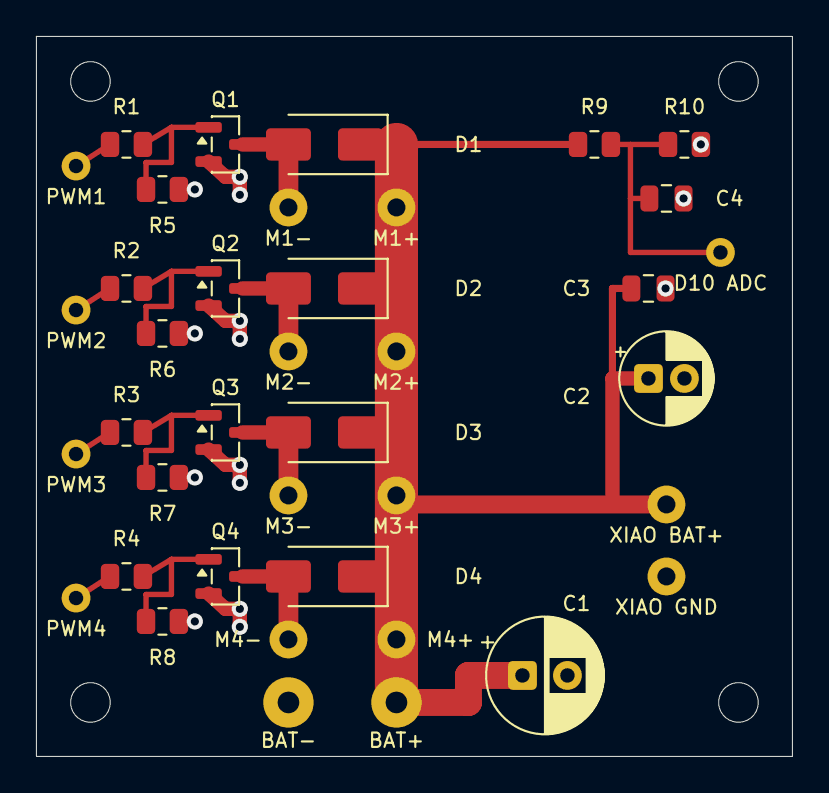
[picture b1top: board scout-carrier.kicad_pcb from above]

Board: 2 copper layers, 42.0 x 40.0 mm, 43 parts (0 on the bottom side), 15 nets.

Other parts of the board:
H1, H2, H3, H4: M2; MountingHole_2.2mm_M2
